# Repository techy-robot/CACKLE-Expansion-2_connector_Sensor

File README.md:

---
modified: 2025-11-07T22:07:14-07:00
---
# 2 connector Sensor Board

> [!TIP]
> This board is part of a larger modular control board ecosystem, [CACKLE](https://github.com/techy-robot/CACKLE)

This is a connector breakout board that spans between 2 vertical mezzanine connectors on a hub. It has one Qwiic connector, two nanoSPI connectors, and header breakouts for the free pins, chip select pins, and the SPI pins. It also has test pads for the RS485 bus. Essentially it breaks out every pin accessible via the mezzanine connectors.

One advantage this has over the single connector breakout is that this fits on normal sized hubs without needing a vertical spacer

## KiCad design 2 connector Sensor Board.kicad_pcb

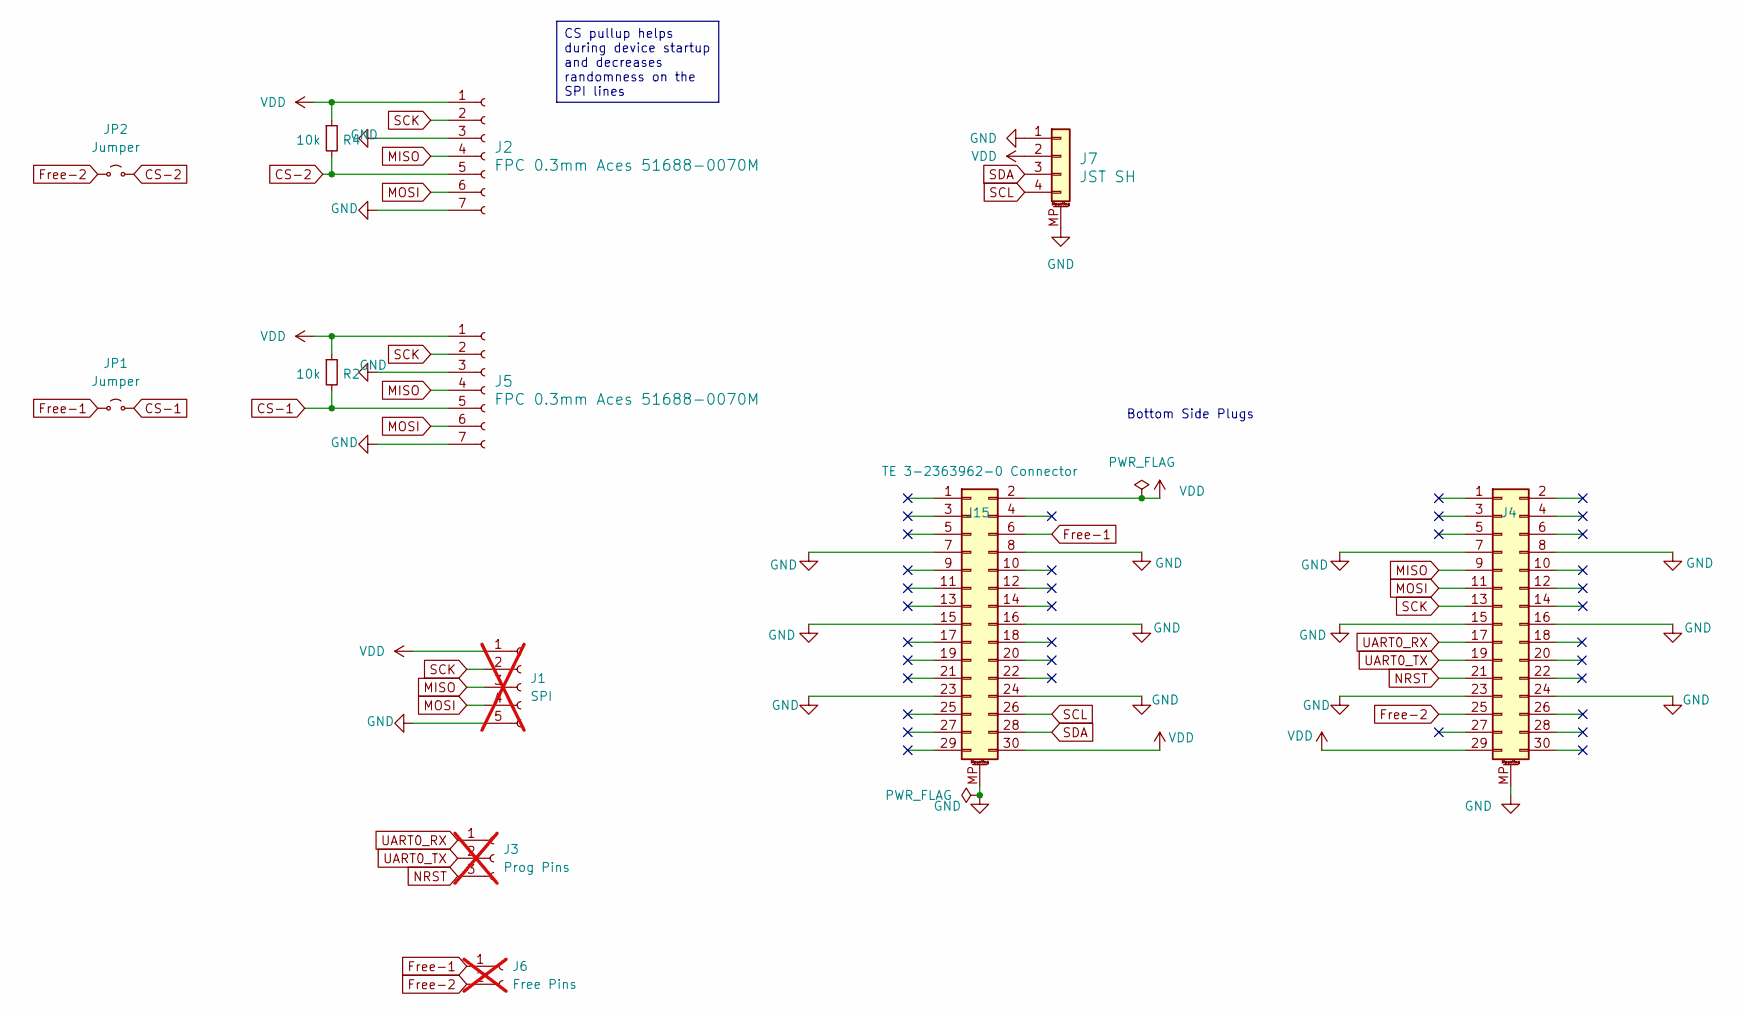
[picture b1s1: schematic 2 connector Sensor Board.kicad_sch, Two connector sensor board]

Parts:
J1: SPI; PinHeader_1x05_P1.27mm_Vertical; not fitted
J2, J5: FPC 0.3mm Aces 51688-0070M; fpc_7pin_0.3mm_connector Panasonic
J3: Prog Pins; PinHeader_1x03_P1.27mm_Vertical; not fitted
J4, J15: TE 3-2363962-0 Connector; TE_mezzanine_conn_3-2363962-0; LCSC C425104
J6: Free Pins; PinHeader_1x02_P1.27mm_Vertical; not fitted
J7: JST SH; JST_SH_SM04B-SRSS-TB_1x04-1MP_P1.00mm_Horizontal; LCSC C160404
JP1, JP2: Jumper; SolderJumper-2_P1.3mm_Open_RoundedPad1.0x1.5mm
R2, R4: 10k; R_0402_1005Metric; LCSC C25744

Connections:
CS-1: J5.5, JP1.2 (B), R2.2
CS-2: J2.5, JP2.2 (B), R4.2
Free-1: J6.1, J15.6, JP1.1 (A)
Free-2: J4.25, J6.2, JP2.1 (A)
GND: J1.5, J2.3, J2.7, J4.7, J4.8, J4.15, J4.16, J4.23, J4.24, J4.MP (MountPin), J5.3, J5.7, J7.1, J7.MP (MountPin), J15.7, J15.8, J15.15, J15.16, J15.23, J15.24, J15.MP (MountPin)
MISO: J1.3, J2.4, J4.9, J5.4
MOSI: J1.4, J2.6, J4.11, J5.6
NRST: J3.3, J4.21
SCK: J1.2, J2.2, J4.13, J5.2
SCL: J7.4, J15.26
SDA: J7.3, J15.28
UART0_RX: J3.1, J4.17
UART0_TX: J3.2, J4.19
VDD: J1.1, J2.1, J4.29, J5.1, J7.2, J15.2, J15.30, R2.1, R4.1

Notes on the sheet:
Bottom Side Plugs
CS pullup helps during device startup and decreases randomness on the SPI lines

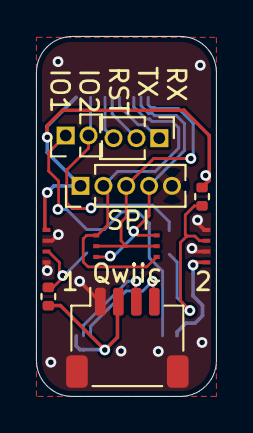
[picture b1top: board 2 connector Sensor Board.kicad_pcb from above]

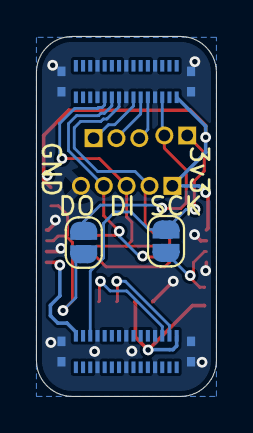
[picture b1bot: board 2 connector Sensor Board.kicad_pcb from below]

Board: 2 copper layers, 10.0 x 20.0 mm, 12 parts (4 on the bottom side), 14 nets.

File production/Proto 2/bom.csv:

Designator,Footprint,Quantity,Value,LCSC Part #
J1,PinHeader_1x05_P1.27mm_Vertical,1,SPI,
"J15, J4",TE_mezzanine_conn_3-2363962-0,2,TE 3-2363962-0 Connector,C425104
"J2, J5",fpc_7pin_0.3mm_connector Panasonic,2,FPC 0.3mm Aces 51688-0070M,
J3,PinHeader_1x03_P1.27mm_Vertical,1,Prog Pins,
J6,PinHeader_1x02_P1.27mm_Vertical,1,Free Pins,
J7,JST_SH_SM04B-SRSS-TB_1x04-1MP_P1.00mm_Horizontal,1,JST SH,C160404
"JP1, JP2",SolderJumper-2_P1.3mm_Open_RoundedPad1.0x1.5mm,2,Jumper,
"R2, R4",0402,2,10k,C25744

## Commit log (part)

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2024-12-31 Rearranged design files
    Instead of "Kicad" the main design folder is now named "Hardware" since I have gerbers and notes besides the kicad files. I have also put my designs in their proper categories.
2025-01-01 Updated files for JLC DFM checks
2025-01-02 Added schematic PDFs for all boards
2025-01-04 Added gerber zip files
2025-01-13 Added README files for each module
2025-01-13 Changed link names for schematic embeds not displayin
    In Obsidian I can see the pdf embeds perfectly fine, but Github doesn't want to show embedded PDFs. I changed the link alias to "Schematic PDF" so people know what the link is when it doesn't display
2025-03-19 Added pictures to each module
    Next I need to add readmes for each!
2025-10-10 Moved all current production files to Proto 1.
    I haven't made a 2nd prototype yet
2025-11-07 Added License
2025-11-08 Updated README with link to main repo
2025-11-10 Added gitignore
2025-11-16 Updated schematic with latest parts and pinout
2025-11-16 Finished reroute
2025-11-16 Finished redesign and export

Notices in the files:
2 connector Sensor Board.kicad_pcb:
Licensed under CERN-OHL-S v2
